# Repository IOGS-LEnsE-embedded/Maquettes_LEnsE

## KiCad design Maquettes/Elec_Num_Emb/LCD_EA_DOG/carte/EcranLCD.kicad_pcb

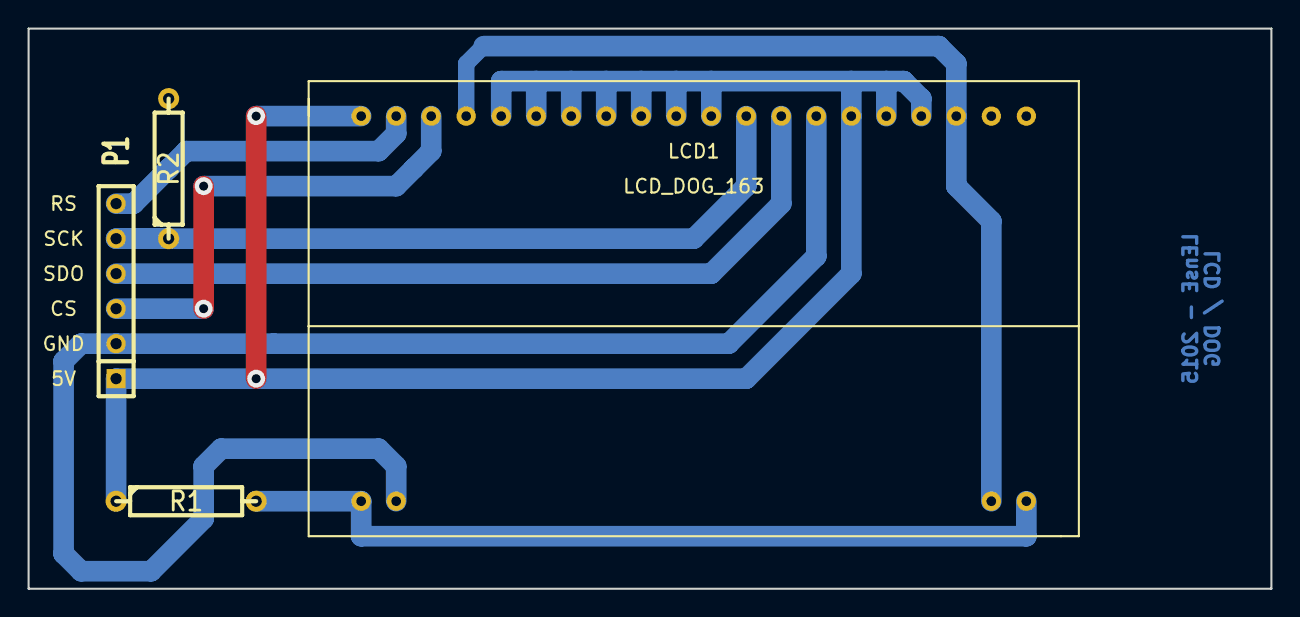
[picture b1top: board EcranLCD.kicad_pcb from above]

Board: 2 copper layers, 90.2 x 40.6 mm, 4 parts (0 on the bottom side), 7 nets.

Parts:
LCD1: LCD_DOG_163; LCD_DOG
P1: CONN_6; SIL-6
R1: 47; R4
R2: 270; R4

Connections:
CS: LCD1.38, P1.3
GND: LCD1.2, LCD1.19, LCD1.23, LCD1.27, LCD1.37, P1.2, R2.2
unnamed: LCD1.1, LCD1.20, R1.2
RS: LCD1.39, P1.6
SCK: LCD1.29, P1.5, R2.1
SDO: LCD1.28, P1.4
VCC: LCD1.24, LCD1.25, LCD1.26, LCD1.30, LCD1.31, LCD1.32, LCD1.33, LCD1.34, LCD1.35, LCD1.36, LCD1.40, P1.1, R1.1

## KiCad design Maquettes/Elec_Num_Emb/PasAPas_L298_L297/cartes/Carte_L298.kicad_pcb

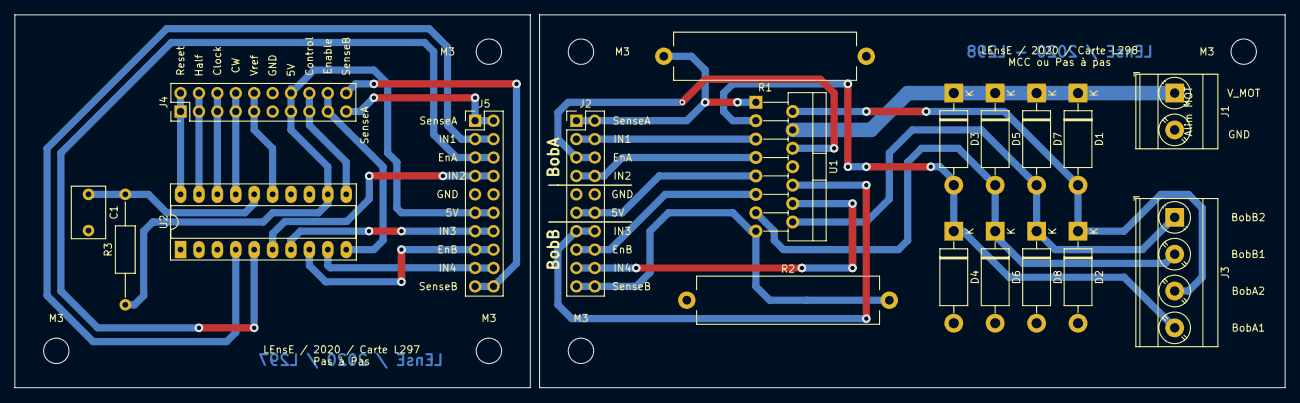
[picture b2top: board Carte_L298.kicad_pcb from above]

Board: 2 copper layers, 175.3 x 51.4 mm, 25 parts (0 on the bottom side), 33 nets.

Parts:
C1: 3.3nF; C_Rect_L7.0mm_W4.5mm_P5.00mm
D1, D2, D3, D4, D5, D6, D7, D8: D; D_DO-15_P12.70mm_Horizontal
J1: Alim_MOT; TerminalBlock_Phoenix_MKDS-3-2-5.08_1x02_P5.08mm_Horizontal
J2: Commande_P; PinHeader_2x10_P2.54mm_Vertical
J3: TO_M1; TerminalBlock_Phoenix_MKDS-3-4-5.08_1x04_P5.08mm_Horizontal
J4: Commande_C; PinHeader_2x10_P2.54mm_Vertical
J5: Commande_CP; PinHeader_2x10_P2.54mm_Vertical
M3, M3#2, M3#3, M3#4, M3#5, M3#6: MountingHole_3.5mm
R1, R2: 0.5; R_Axial_Power_L25.0mm_W6.4mm_P27.94mm
R3: 22k; R_Axial_DIN0207_L6.3mm_D2.5mm_P15.24mm_Horizontal
U1: L298HN; TO-220-15_P2.54x2.54mm_StaggerOdd_Lead4.58mm_Vertical
U2: L297; DIP-20_W7.62mm_Socket_LongPads

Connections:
5V: J2.11, J2.12, U1.9
5V_C: J4.13, J4.14, J5.11, J5.12, R3.1, U2.12
/BobA1: D3.2, D4.1, J3.4, U1.3
/BobA2: D1.2, D2.1, J3.3, U1.2
/BobB1: D5.2, D6.1, J3.2, U1.13
/BobB2: D7.2, D8.1, J3.1, U1.14
CLOCK: J4.5, J4.6, U2.18
CONTROL: J4.15, J4.16, U2.11
CW: J4.7, J4.8, U2.17
ENABLE: J4.17, J4.18, U2.10
EnA: J2.5, J2.6, U1.6
EnA_C: J5.5, J5.6, U2.5
EnB: J2.15, J2.16, U1.11
EnB_C: J5.15, J5.16, U2.8
GND: D2.2, D4.2, D6.2, D8.2, J1.2, J2.9, J2.10, R1.1, R2.1, U1.8
GND_C: C1.2, J4.11, J4.12, J5.9, J5.10, U2.2, U2.13, U2.14
HALF: J4.3, J4.4, U2.19
IN1: J2.3, J2.4, U1.5
IN1_C: J5.3, J5.4, U2.4
IN2: J2.7, J2.8, U1.7
IN2_C: J5.7, J5.8, U2.6
IN3: J2.13, J2.14, U1.10
IN3_C: J5.13, J5.14, U2.7
IN4: J2.17, J2.18, U1.12
IN4_C: J5.17, J5.18, U2.9
unnamed: C1.1, R3.2, U2.16
RESET: J4.1, J4.2, U2.20
SenseA: J2.1, J2.2, R1.2, U1.1
SenseA_C: J4.19, J5.1, J5.2
SenseB: J2.19, J2.20, R2.2, U1.15
SenseB_C: J4.20, J5.19, J5.20
VREF_C: J4.9, J4.10, U2.15
V_MOT: D1.1, D3.1, D5.1, D7.1, J1.1, U1.4

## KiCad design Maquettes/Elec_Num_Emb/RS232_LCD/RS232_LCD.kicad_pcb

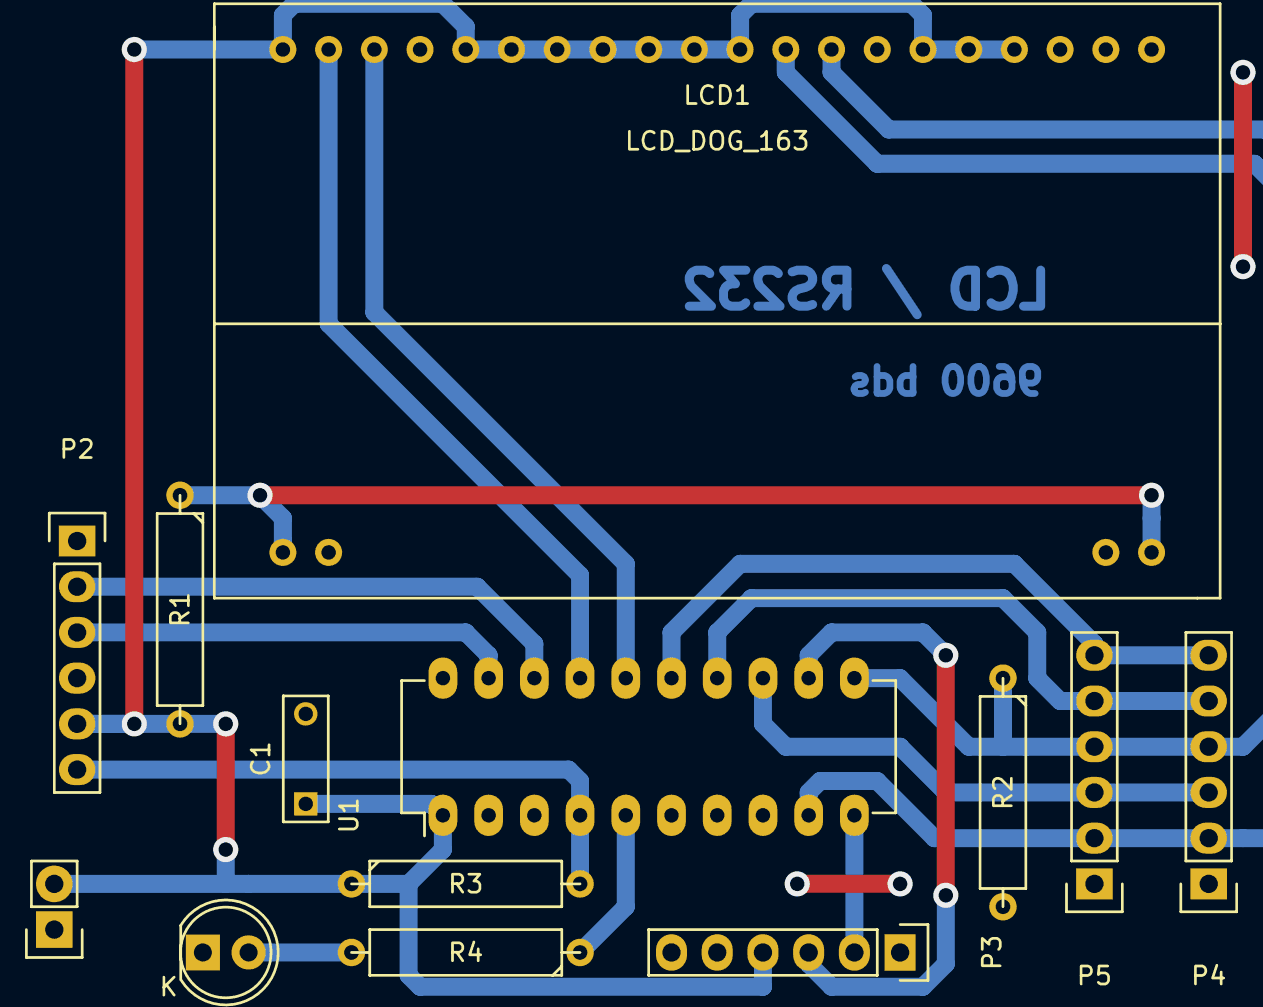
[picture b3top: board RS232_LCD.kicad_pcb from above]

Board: 2 copper layers, 13 parts (0 on the bottom side), 17 nets.

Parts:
C1: 100nF; C_Rect_L7_W2.5_P5
D1: LED; LED-5MM
LCD1: LCD_DOG_163; LCD_DOG
P1: CONN_01X02; Pin_Header_Straight_1x02
P2, P3, P4, P5: CONN_01X06; Pin_Header_Straight_1x06
R1: 47; R5
R2: 270; R5
R3: 1.2k; R5
R4: 100; R5
U1: PIC16F1509; DIP-20_W7.62mm_LongPads

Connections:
CS: LCD1.38, U1.16
CS1: P4.6, P5.6, U1.15
CS2: P4.5, P5.5, U1.14
GND: C1.2, D1.1, LCD1.2, LCD1.19, LCD1.23, LCD1.27, LCD1.37, P1.1, P2.4, P3.6, P4.1, P5.1, R2.2, U1.20
MCLR: P2.6, R3.2, U1.4
MISO: P4.3, P5.3, U1.13
MOSI: LCD1.28, P4.2, P5.2, U1.9
unnamed: D1.2, R4.2
unnamed: LCD1.1, LCD1.20, R1.1
unnamed: R4.1, U1.5
PGC: P2.2, U1.18
PGD: P2.3, U1.19
RS: LCD1.39, U1.17
RX: P3.2, U1.10
SCK: LCD1.29, P4.4, P5.4, R2.1, U1.11
TX: P3.3, U1.12
VCC: C1.1, LCD1.24, LCD1.25, LCD1.26, LCD1.30, LCD1.31, LCD1.32, LCD1.33, LCD1.34, LCD1.35, LCD1.36, LCD1.40, P1.2, P2.5, P3.4, R1.2, R3.1, U1.1

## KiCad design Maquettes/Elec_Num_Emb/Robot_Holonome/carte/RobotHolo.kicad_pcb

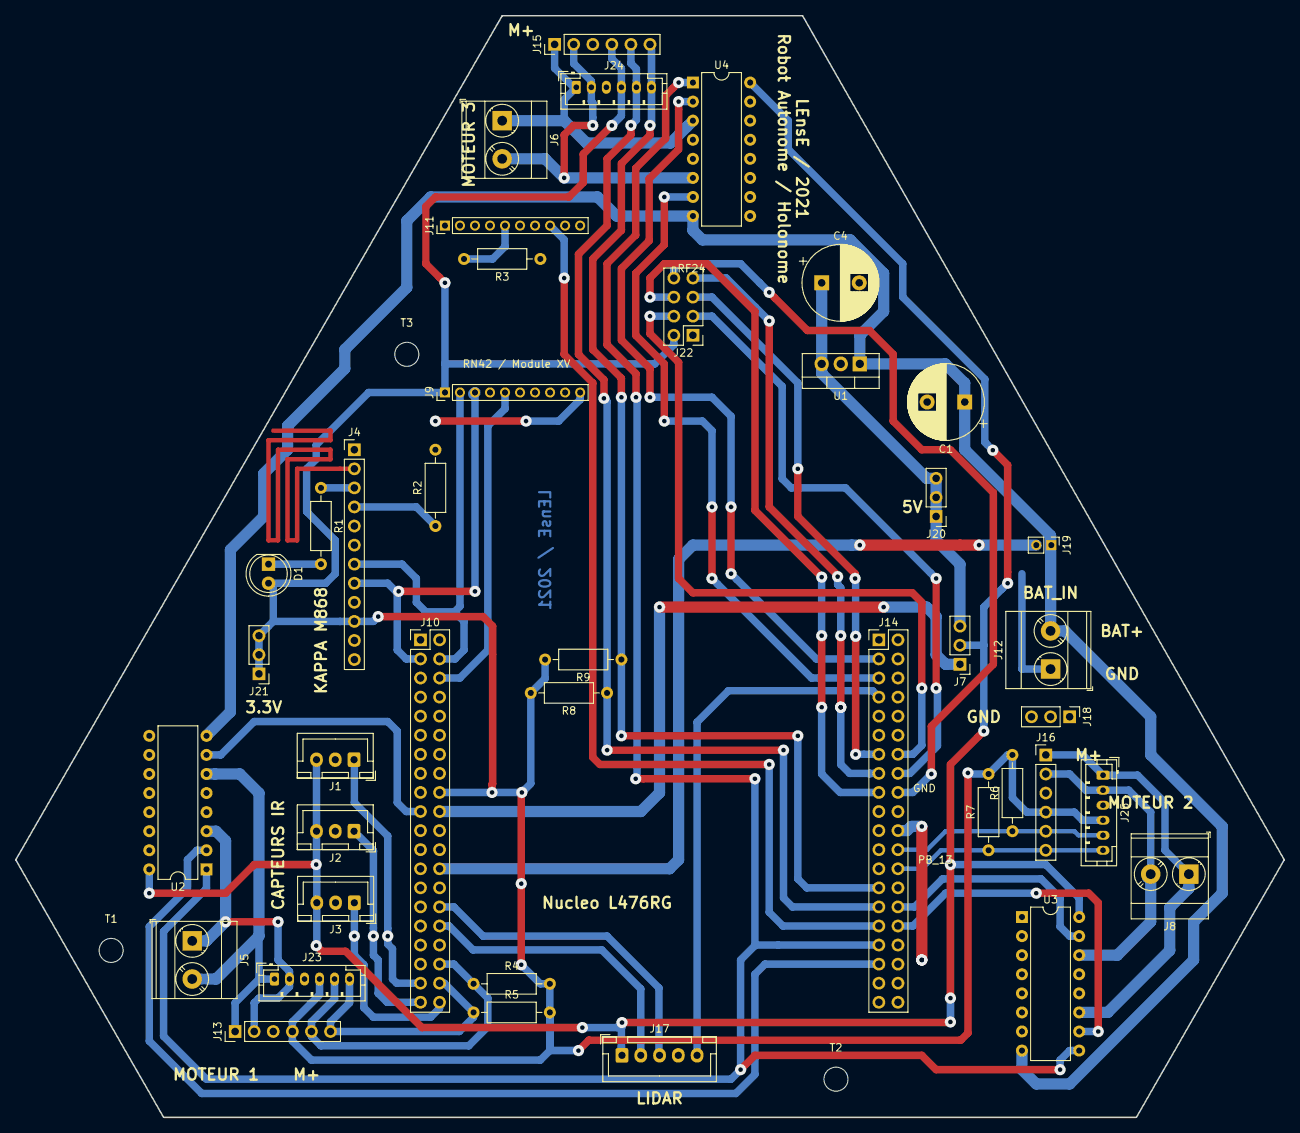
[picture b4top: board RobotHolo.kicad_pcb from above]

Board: 2 copper layers, 168.9 x 146.7 mm, 44 parts (0 on the bottom side), 46 nets.

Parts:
C1, C4: 10uF; CP_Radial_D10.0mm_P5.00mm
D1: LED; LED_D5.0mm_Clear
J1: Capt1; JST_XH_B03B-XH-A_1x03_P2.50mm_Vertical
J2: Capt2; JST_XH_B03B-XH-A_1x03_P2.50mm_Vertical
J3: Capt3; JST_XH_B03B-XH-A_1x03_P2.50mm_Vertical
J4: Kappa_M868; PinHeader_1x12_P2.54mm_Vertical
J5: MOT_1; TerminalBlock_Phoenix_MKDS-3-2-5.08_1x02_P5.08mm_Horizontal
J6: MOT_3; TerminalBlock_Phoenix_MKDS-3-2-5.08_1x02_P5.08mm_Horizontal
J7: 5V_Select; PinHeader_1x03_P2.54mm_Vertical
J8: MOT_2; TerminalBlock_Phoenix_MKDS-3-2-5.08_1x02_P5.08mm_Horizontal
J9: RN42X-GAUCHE; PinHeader_1x10_P2.00mm_Vertical
J10: Morpho_Gauche; PinHeader_2x20_P2.54mm_Vertical
J11: RN42X-DROITE; PinHeader_1x10_P2.00mm_Vertical
J12: BAT_IN; TerminalBlock_Phoenix_MKDS-3-2-5.08_1x02_P5.08mm_Horizontal
J13: Moteur1; PinHeader_1x06_P2.54mm_Vertical
J14: Morpho_Droite; PinHeader_2x20_P2.54mm_Vertical
J15: Moteur3; PinHeader_1x06_P2.54mm_Vertical
J16: Moteur2; PinHeader_1x06_P2.54mm_Vertical
J17: RPLidar; JST_XH_B05B-XH-A_1x05_P2.50mm_Vertical
J18: GND_reg; PinHeader_1x03_P2.54mm_Vertical
J19: ExternalPower; PinHeader_1x02_P2.00mm_Vertical
J20: 5V_reg; PinHeader_1x03_P2.54mm_Vertical
J21: 3.3V_reg; PinHeader_1x03_P2.54mm_Vertical
J22: Conn_02x04_Odd_Even; PinHeader_2x04_P2.54mm_Vertical
J23, J24: Moteur1bis; JST_PH_B6B-PH-K_1x06_P2.00mm_Vertical
J25: Moteur2bis; JST_PH_B6B-PH-K_1x06_P2.00mm_Vertical
R1: 120; R_Axial_DIN0207_L6.3mm_D2.5mm_P10.16mm_Horizontal
R2: 8.2k; R_Axial_DIN0207_L6.3mm_D2.5mm_P10.16mm_Horizontal
R3, R4, R5, R6, R7, R8, R9: 1k; R_Axial_DIN0207_L6.3mm_D2.5mm_P10.16mm_Horizontal
T1, T2, T3: MountingHole_3.2mm_M3
U1: L7805; TO-220-3_Vertical
U2, U3, U4: L293D; DIP-16_W7.62mm

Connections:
3.3V: D1.2, J4.10, J9.1, J10.18, J13.4, J15.4, J16.4, J21.1, J21.2, J21.3, J22.2, J23.4, J24.4, J25.4, R4.2, R5.2, R6.2, R7.2, R8.2, R9.2
5V: J1.3, J2.3, J3.3, J7.2, J17.1, U2.16, U3.16, U4.16
5V_NUC: J7.1, J10.20
5V_REG: C4.1, J7.3, J20.1, J20.2, J20.3, U1.3
EnaPower: J14.33, U2.1, U3.9, U4.1
GND: C1.2, C4.2, J1.2, J2.2, J3.2, J4.1, J4.11, J9.10, J10.21, J10.22, J10.24, J12.1, J13.3, J14.22, J15.3, J16.3, J17.4, J18.1, J18.2, J18.3, J22.1, J23.3, J24.3, J25.3, R2.2, R3.1, U1.2, U2.4, U2.5, U2.12, U2.13, U3.4, U3.5, U3.12, U3.13, U4.4, U4.5, U4.12, U4.13
GPIO2_STATUS: J11.8, J14.31
Lidar_MOT: J14.7, J17.5
M1_1: J5.1, J13.2, J23.2, U2.3
M1_2: J5.2, J13.1, J23.1, U2.6
M1_A: J10.36, J13.5, J23.5, R4.1
M1_B: J10.38, J13.6, J23.6, R5.1
M2_1: J8.2, J16.2, J25.2, U3.14
M2_2: J8.1, J16.1, J25.1, U3.11
M2_A: J14.24, J16.5, J25.5, R6.1
M2_B: J14.26, J16.6, J25.6, R7.1
M3_1: J6.2, J15.2, J24.2, U4.6
M3_2: J6.1, J15.1, J24.1, U4.3
M3_A: J14.29, J15.5, J24.5, R8.1
M3_B: J14.27, J15.6, J24.6, R9.1
Mot1_D1: J14.35, U2.2
Mot1_D2: J10.19, U2.7
Mot2_D1: J14.30, U3.15
Mot2_D2: J14.32, U3.10
Mot3_D1: J14.3, U4.2
Mot3_D2: J14.5, U4.7
NUC_VIN: J10.26, J19.2
unnamed: D1.1, R1.2
unnamed: J4.3, R1.1
unnamed: J4.4, R2.1
unnamed: J11.5, R3.2
RESET_N: J9.5, J10.6
RX: J4.7, J9.2, J10.4
RX_4: J10.32, J17.2
TX: J4.8, J9.3, J10.3
TX_4: J10.30, J17.3
VCapt1: J1.1, J10.37
VCapt2: J2.1, J10.39
VCapt3: J3.1, J10.40
VIN: C1.1, J12.2, J19.1, U1.1, U2.8, U3.8, U4.8
nRF_CE: J14.16, J22.3
nRF_CSN: J14.14, J22.4
nRF_IRQ: J14.18, J22.8
nRF_MISO: J14.15, J22.7
nRF_MOSI: J14.17, J22.6
nRF_SCK: J14.13, J22.5

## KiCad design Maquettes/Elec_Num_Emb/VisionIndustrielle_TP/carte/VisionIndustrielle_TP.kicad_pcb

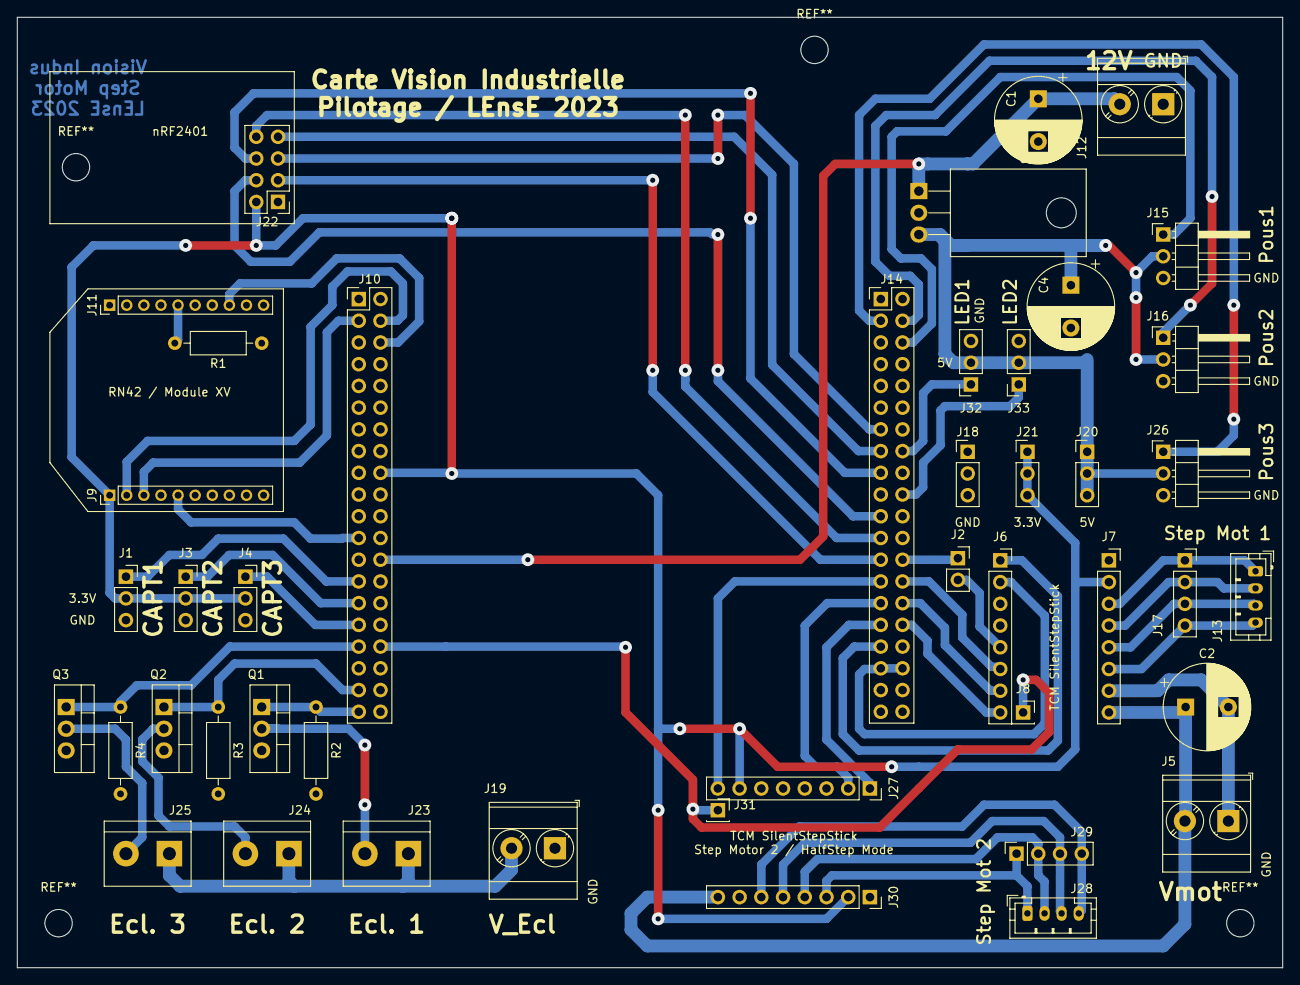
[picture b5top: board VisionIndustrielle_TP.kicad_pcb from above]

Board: 2 copper layers, 148.0 x 111.1 mm, 44 parts (0 on the bottom side), 50 nets.

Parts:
C1, C2, C4: 10uF; CP_Radial_D10.0mm_P5.00mm
J1: Capt1; PinSocket_1x03_P2.54mm_Vertical
J2: CFG3_Open; PinSocket_1x02_P2.54mm_Vertical
J3: Capt2; PinSocket_1x03_P2.54mm_Vertical
J4: Capt3; PinSocket_1x03_P2.54mm_Vertical
J5: VMOT; TerminalBlock_Phoenix_MKDS-3-2-5.08_1x02_P5.08mm_Horizontal
J6: TMC2100_A; PinSocket_1x08_P2.54mm_Vertical
J7: TMC2100_B; PinSocket_1x08_P2.54mm_Vertical
J8, J31: TMC2100_Vref; PinSocket_1x01_P2.54mm_Vertical
J9: RN42X-GAUCHE; PinHeader_1x10_P2.00mm_Vertical
J10: Morpho_Gauche; PinHeader_2x20_P2.54mm_Vertical
J11: RN42X-DROITE; PinHeader_1x10_P2.00mm_Vertical
J12: BAT_IN; TerminalBlock_Phoenix_MKDS-3-2-5.08_1x02_P5.08mm_Horizontal
J13: Motor1_Out_JST; JST_PH_B4B-PH-K_1x04_P2.00mm_Vertical
J14: Morpho_Droite; PinHeader_2x20_P2.54mm_Vertical
J15: Poussoir1; PinHeader_1x03_P2.54mm_Horizontal
J16: Poussoir2; PinHeader_1x03_P2.54mm_Horizontal
J17: Motor1_Out_Pin; PinSocket_1x04_P2.54mm_Vertical
J18: GND_reg; PinHeader_1x03_P2.54mm_Vertical
J19: V_ECLAIRAGE; TerminalBlock_Phoenix_MKDS-3-2-5.08_1x02_P5.08mm_Horizontal
J20: 5V_reg; PinHeader_1x03_P2.54mm_Vertical
J21: 3.3V_reg; PinHeader_1x03_P2.54mm_Vertical
J22: nRF24L01; PinHeader_2x04_P2.54mm_Vertical
J23: V_Ecl_1; TerminalBlock_bornier-2_P5.08mm
J24: V_Ecl_2; TerminalBlock_bornier-2_P5.08mm
J25: V_Ecl_3; TerminalBlock_bornier-2_P5.08mm
J26: Poussoir3; PinHeader_1x03_P2.54mm_Horizontal
J27: TMC2100_A_b; PinSocket_1x08_P2.54mm_Vertical
J28: Motor2_Out_JST; JST_PH_B4B-PH-K_1x04_P2.00mm_Vertical
J29: Motor2_Out_Pin; PinSocket_1x04_P2.54mm_Vertical
J30: TMC2100_B_b; PinSocket_1x08_P2.54mm_Vertical
J32: LED Strip 1; PinSocket_1x03_P2.54mm_Vertical
J33: LED Strip 2; PinSocket_1x03_P2.54mm_Vertical
Q1, Q2, Q3: IRL540N; TO-220-3_Vertical
R1: 1k; R_Axial_DIN0207_L6.3mm_D2.5mm_P10.16mm_Horizontal
R2, R3, R4: 8.2k; R_Axial_DIN0207_L6.3mm_D2.5mm_P10.16mm_Horizontal
U1: L7805; TO-220-3_Horizontal_TabDown

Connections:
3.3V_NUC: J1.2, J3.2, J4.2, J7.2, J9.1, J10.18, J21.1, J21.2, J21.3, J22.2, J27.7, J30.2
5V_REG: C4.1, J15.2, J16.2, J20.1, J20.2, J20.3, J26.2, J32.2, J33.2, U1.3
CE_nRF: J14.25, J22.3
CFG1_NUC: J6.7, J14.30
CFG2_NUC: J6.6, J14.28
CFG3_NUC: J2.1, J14.26
CFG3_NUC_O: J2.2, J6.5
CSN_nRF: J14.21, J22.4
DIR2_NUC: J14.31, J27.1
DIR_NUC: J6.1, J14.33
EN2_NUC: J14.27, J27.8
EN_NUC: J6.8, J14.32
GND: C1.2, C2.2, C4.2, J1.3, J3.3, J4.3, J5.1, J7.1, J7.7, J9.10, J10.21, J10.22, J10.24, J12.1, J14.22, J15.3, J16.3, J18.1, J18.2, J18.3, J19.1, J22.1, J26.3, J27.6, J30.1, J30.7, J32.3, J33.3, Q1.3, Q2.3, Q3.3, R1.1, R2.2, R3.2, R4.2, U1.2
GPIO2_STATUS: J10.6, J11.8
IRQ_nRF: J14.23, J22.8
LED_1: J14.16, J32.1
LED_2: J14.20, J33.1
MISO: J14.15, J22.7
MOSI: J14.17, J22.6
MOT2_1A: J28.1, J29.1, J30.3
MOT2_1B: J28.2, J29.2, J30.4
MOT2_2A: J28.3, J29.3, J30.5
MOT2_2B: J28.4, J29.4, J30.6
MOT_1A: J7.3, J13.1, J17.1
MOT_1B: J7.4, J13.2, J17.2
MOT_2A: J7.5, J13.3, J17.3
MOT_2B: J7.6, J13.4, J17.4
NUC_E1: J10.39, Q1.1, R2.1
NUC_E2: J10.37, Q2.1, R3.1
NUC_E3: J10.33, Q3.1, R4.1
NUC_P1: J14.6, J15.1
NUC_P2: J14.4, J16.1
NUC_P3: J14.3, J26.1
unnamed: J11.5, R1.2
unnamed: J23.2, Q1.2
unnamed: J24.2, Q2.2
unnamed: J25.2, Q3.2
RESET_N: J9.5, J10.23
RX: J9.2, J10.4
SCK: J14.13, J22.5
STEP2_NUC: J14.29, J27.2
STEP_NUC: J6.2, J14.35, J14.36
TX: J9.3, J10.3
VCapt1: J1.1, J10.27
VCapt2: J3.1, J10.29
VCapt3: J4.1, J10.31
VECL: J19.2, J23.1, J24.1, J25.1
VIN: C1.1, J10.26, J12.2, U1.1
VMOT: C2.1, J5.2, J7.8, J30.8
VREF_OUT_NUC: J8.1, J10.34, J31.1

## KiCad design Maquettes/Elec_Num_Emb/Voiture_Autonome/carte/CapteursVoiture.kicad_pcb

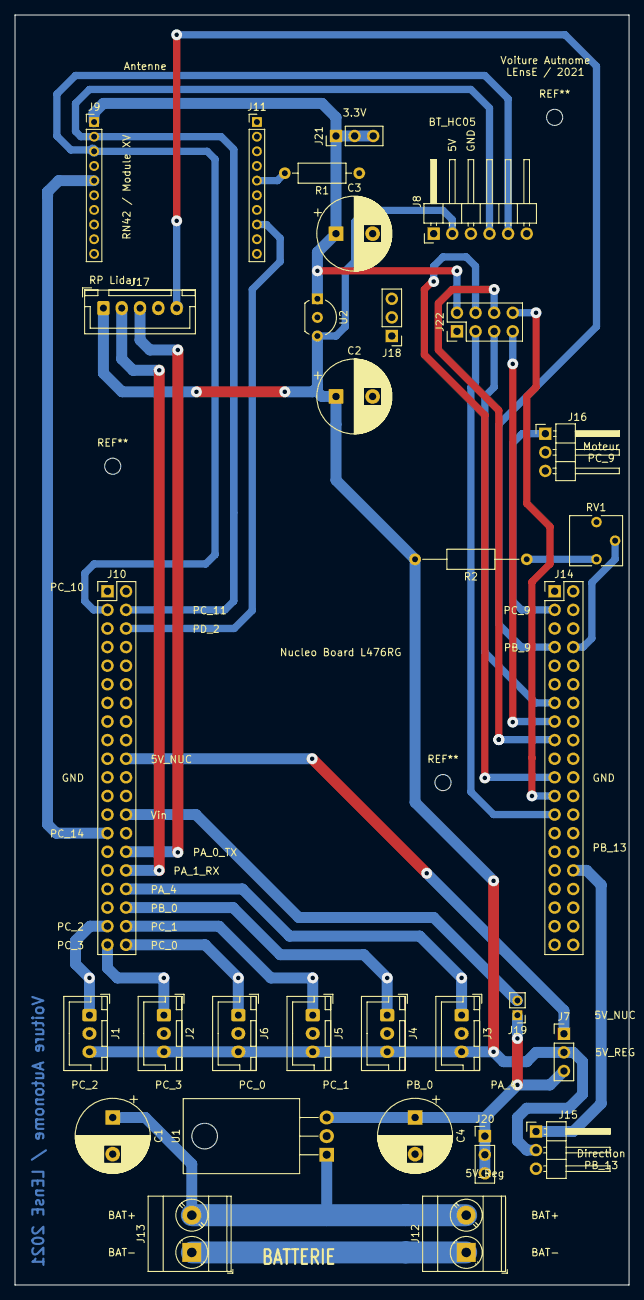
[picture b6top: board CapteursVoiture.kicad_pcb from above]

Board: 2 copper layers, 83.8 x 173.4 mm, 31 parts (0 on the bottom side), 31 nets.

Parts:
C1, C2, C3, C4: 10uF; CP_Radial_D10.0mm_P5.00mm
J1: Capt1; JST_XH_B3B-XH-A_1x03_P2.50mm_Vertical
J2: Capt2; JST_XH_B3B-XH-A_1x03_P2.50mm_Vertical
J3: Capt3; JST_XH_B3B-XH-A_1x03_P2.50mm_Vertical
J4: Capt4; JST_XH_B3B-XH-A_1x03_P2.50mm_Vertical
J5: Capt5; JST_XH_B3B-XH-A_1x03_P2.50mm_Vertical
J6: CaptLD; JST_XH_B3B-XH-A_1x03_P2.50mm_Vertical
J7: 5V_Select; PinHeader_1x03_P2.54mm_Vertical
J8: BT_HC05; PinHeader_1x06_P2.54mm_Horizontal
J9: RN42X-GAUCHE; PinHeader_1x10_P2.00mm_Vertical
J10: Morpho_Gauche; PinHeader_2x20_P2.54mm_Vertical
J11: RN42X-DROITE; PinHeader_1x10_P2.00mm_Vertical
J12: BAT_IN; TerminalBlock_Phoenix_MKDS-3-2-5.08_1x02_P5.08mm_Horizontal
J13: BAT_OUT; TerminalBlock_Phoenix_MKDS-3-2-5.08_1x02_P5.08mm_Horizontal
J14: Morpho_Droite; PinHeader_2x20_P2.54mm_Vertical
J15: Direction; PinHeader_1x03_P2.54mm_Horizontal
J16: Motorisation; PinHeader_1x03_P2.54mm_Horizontal
J17: RPLidar; JST_XH_B5B-XH-A_1x05_P2.50mm_Vertical
J18: GND_reg; PinHeader_1x03_P2.54mm_Vertical
J19: ExternalPower; PinHeader_1x02_P2.00mm_Vertical
J20: 5V_reg; PinHeader_1x03_P2.54mm_Vertical
J21: 3.3V_reg; PinHeader_1x03_P2.54mm_Vertical
J22: nRF24L01; PinHeader_2x04_P2.54mm_Vertical
R1: 1k; R_Axial_DIN0207_L6.3mm_D2.5mm_P10.16mm_Horizontal
R2: 5.1k; R_Axial_DIN0207_L6.3mm_D2.5mm_P15.24mm_Horizontal
RV1: POT_10k; Potentiometer_Vishay_T73YP_Vertical
U1: L7805; TO-220-3_Horizontal_TabDown
U2: L78L33_TO92; TO-92L_Inline_Wide

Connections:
3.3V: C3.1, J9.1, J21.1, J21.2, J21.3, J22.2, U2.1
5V: C2.1, J1.3, J2.3, J3.3, J4.3, J5.3, J6.3, J7.2, J8.2, J15.2, J17.1, R2.2, U2.3
5V_NUC: J7.1, J10.20
5V_REG: C4.1, J7.3, J19.1, J20.1, J20.2, J20.3, U1.3
5V_REG_VIN: J10.26, J19.2
CE_nRF: J14.25, J22.3
CSN_nRF: J14.21, J22.4
GND: C1.2, C2.2, C3.2, C4.2, J1.2, J2.2, J3.2, J4.2, J5.2, J6.2, J8.3, J9.10, J10.21, J10.22, J10.24, J12.1, J13.1, J14.22, J15.3, J16.3, J17.4, J18.1, J18.2, J18.3, J22.1, R1.1, RV1.3, U1.2, U2.2
GPIO2_STATUS: J10.6, J11.8
IRQ_nRF: J14.23, J22.8
Lidar_MOT: J14.7, J17.5
MISO: J14.15, J22.7
MOSI: J14.17, J22.6
NUC_DIR: J14.32, J15.1
NUC_MOT: J14.3, J16.1
unnamed: J11.5, R1.2
unnamed: R2.1, RV1.1
RESET_N: J9.5, J10.27
RX: J8.4, J9.2, J10.4
RX_4: J10.32, J17.2
SCK: J14.13, J22.5
TX: J8.5, J9.3, J10.3
TX_4: J10.30, J17.3
VCapt1: J1.1, J10.37
VCapt2: J2.1, J10.39
VCapt3: J3.1, J10.34
VCapt4: J4.1, J10.36
VCapt5: J5.1, J10.38
VCaptLD: J6.1, J10.40
VIN: C1.1, J12.2, J13.2, U1.1
VPOT: J14.8, RV1.2
